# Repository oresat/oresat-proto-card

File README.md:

# "oresat-proto-card"

This is the "prototype" card for OreSat, meant to pioneer future cards and test the backplane, and be an 
easy way to hack in functionality. NOT MEANT FOR FLIGHT.

## Features

- Populates the two 1.27 mm connectors from the backplane.
- Populates all three SMPM RF connectors from the backplane.
- Standard TPS63070-bsaed buck/boost SPS (Vin = 2.5 to 7 V, Vout = 3.3V)
- Has our standard/favorite STM32F042K6 microcontroller.
   - With SWD, UART (FTDI), and CAN (to the backplane).
- Has lots of breakouts, but DO NOT POPULATE THE 0.1 IN CONNECTORS, THEY'RE TOO TALL!!!

## Connector information

- Main 1.27 mm connector ("Center" connector)
   - Samtec TFM-120-01-L-D-RA
   - https://www.digikey.com/products/en?lang=en&site=US&keywords=TFM-120-01-L-D-RA
   - Drawing: http://suddendocs.samtec.com/prints/tfm-1xx-xx-xxx-d-xxx-mkt.pdf
   - Brochure: http://suddendocs.samtec.com/catalog_english/tfm.pdf
   - 3D CAD: https://www.samtec.com/partnumber/tfm-120-01-l-d-ra?vendor=digikey#technical
   - Notes: the -RE1 model is better because of the solder stakes, but the female connector doesn't fit! The stakes get in the way :(

- Auxiliary 1.27 mm ("alt-left" connector)
   - Samtec TFM-110-01-L-D-RA

- RF (70 cm, L band, S band) conenctors
   - Card
      - Molex 73300-0030 (possible replacement is 73300-0020 but it has full detent that we don't want)
      - SMPM Connector Plug, Male Pin 50 Ohm Board Edge, Cutout; Surface Mount Solder, smooth bore
      - Molex w/3D: https://www.molex.com/molex/products/datasheet.jsp?part=active/0733000030_RF_COAX_CONNECTORS.xml
   - Barrell (connects card to backplane)
      - Molex 73300-0220 (alt but slightly different lengths: -0223, -0228)
      - SMPM female to female barrel adapter 
      - RF Adapters - In Series SMPM JACK/JACK BULLET .21IN
      - Molex w/3D: https://www.molex.com/molex/products/datasheet.jsp?part=active/0733000220_RF_COAX_CONNECTORS.xml

## LICENSE

Copyright Portland State Aerospace Society 2018.

This documentation describes Open Hardware and is licensed under the CERN OHL v. 1.2.

You may redistribute and modify this documentation under the terms of the CERN OHL v.1.2. [http://ohwr.org/cernohl](http://ohwr.org/cernohl). This documentation is distributed WITHOUT ANY EXPRESS OR IMPLIED WARRANTY, INCLUDING OF MERCHANTABILITY, SATISFACTORY QUALITY AND FITNESS FOR A PARTICULAR PURPOSE. Please see the CERN OHL v.1.2 for applicable conditions.

## Version Information

Version | Date       | Notes
--------|------------|-------------------------
3.0     | 2018/11/22 | Big changes in structure, mostly springs. Changed RF connectors to SMPM. Optimized layout for more proto area. 
2.0     | 2018/03/?? | New 1.27 mm connectors, again.
1.0     | ??         | New connectors.

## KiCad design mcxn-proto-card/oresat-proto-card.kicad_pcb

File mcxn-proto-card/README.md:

---
title: "**OreSat MCXN Proto Card**"
subtitle: |
  **Fabrication and Assembly Information**\
  For build TIME-STAMP
fontsize: 10pt
geometry:
  - margin=0.5in
toc: true
toc-depth: 2
colorlinks: true
urlcolor: blue
---

\newpage

# About this Board

## Board Description

The OreSat MCXN Proto Card is a generic OreSat card based on the NXP MCXN947 microcontroller. It has an OreSat Power Domain (OPD), 
a CAN interface, an OreSat Card Debug port, a bzillion test points, and a 0.1 inch hole prototyping area.

The proto card also has the OreSat auxiliary connector and 3 RF backplane connectors, but these are not placed since they're not usually used.

## Documentation Links

- Git repository: <https://github.com/oresat/oresat-flatsat>
- Design Notes can be found [here](https://docs.google.com/document/d/1n5go-qSHrDDtgpcY3E4sctoJmh-bkNlo19UB8_QK84I/edit?usp=sharing)

## Documentation Files

| Filename                        | Notes                                    |
| ------------------------------- | ---------------------------------------- |
| README.pdf                      | This README file                         |
| PROJECT-NAME-outline.dxf        | Board outline (with holes) in DXF format |
| PROJECT-NAME-pcba.step          | 3D model of PCBA (with components)       |
| PROJECT-NAME-render-bot.jpg     | Render of the top of the 3D model        |
| PROJECT-NAME-render-bot.jpg     | Render of the bottom of the 3D model     |
| PROJECT-NAME-schematic.pdf      | PDF of board schematics                  |

## Contact Information

- Website: <https://www.oresat.org/>
- Email: <oresat@pdx.edu>
- Instagram: @pdxaerospace

## Board Renders

{width=50%}
{width=50%}

\newpage

# Printed Circuit Board (PCB) Fabrication Information

## Board Info

- 4 layer board
- Bounding box is 99.8 x 94.6 mm
- Board thickness is 1.59 mm

## Board Requirements

- Design Rules
    - Minimum Trace / Space design rules
       - Outer layers: 0.127 mm (5.0 mil) / 0.127 mm (5.0 mil)
       - Inner layers: 0.127 mm (5.0 mil) / 0.127 mm (5.0 mil)
    - Outer dimension router tolerance: +/- 0.254 mm (10.0 mil)
    - Hole placement tolerance: +/- 0.075 mm (3.0 mil)
    - Inner tab routed slot tolerance: +/- 0.254 mm (10.0 mil)
- Drills
   - Drill Positional Tolerance: 0.051 mm (2.0 mil)
   - Drill Size tolerance: +/- 0.064 mm (2.5 mil)
- Plated/Un-plated holes
  - Via/PTH minimum diameter: 0.254 mm (10 mil)
  - Via/PTH minimum annulus: 0.102 mm (4 mil) radius
- Outline/Routing
  - This board requires a 1 mm router bit.
- Slots
  - There are no slots.
- Cutouts
  - There are no cutouts
- There are 3 fiducials on the top layer.
- Panel tabs ("mouse bites")
   - Card edges must be smooth; no mouse bites or other intrusions into the card outline.
   - If external mouse bites are required, minimize and customer will remove by hand before assembly.
- If not otherwise specified, build to IPC 6012 Class 2 or better.

## Stackup /  Materials

- Outside copper layers is 1 oz Cu after plating (0.043 mm / 1.7 mil)
- Inside copper layers are 0.5 oz Cu (0.018 mm / 0.7 mil)
- There are no requirements on the prepreg or core of this four layer stackup.
- Board Surface treatment should be ENIG, althogh immersion Silver is acceptable.
- White silkscreen on top and bottom surface
- Taiyo PSR-4000 or equivalent soldermask on top and bottom, no requirements for color.

## Array / Panel Information

- Coordinate with Contract Manufacturer (CM) for optimal size of this panel.
- If no feedback from CM, then produce single boards (no panel).

## Fabrication Files

### IPC-2581 File

| Filename                 | Notes                                   |
| ------------------------ | --------------------------------------- |
| PROJECT-NAME-ipc2581.xml | IPC-2581 board information file         |

### Legacy PCB Files

| Filename                      | Notes                                         |
| ------------------------------| --------------------------------------------- |
| PROJECT-NAME-Edge_Cuts.gbr    | RS274X file for the dimension (outline) layer |
| PROJECT-NAME-F_Silkscreen.gbr | RS274X file for the top silkscreen            |
| PROJECT-NAME-F_Mask.gbr       | RS274X file for the top soldermask            |
| PROJECT-NAME-F_Cu.gbr         | RS274X file for the top copper layer          |
| PROJECT-NAME-In1_Cu.gbr       | RS274X file for the layer 2 copper            |
| PROJECT-NAME-In2_Cu.gbr       | RS274X file for the layer 3 copper            |
| PROJECT-NAME-B_Cu.gbr         | RS274X file for the bottom copper layer       |
| PROJECT-NAME-B_Mask.gbr       | RS274X file for the bottom soldermask         |
| PROJECT-NAME-B_Silkscreen.gbr | RS274X file for the bottom silkscreen         |
| PROJECT-NAME-NPTH.drl         | Excellon file for non-plated through holes    |
| PROJECT-NAME-PTH.drl          | Excellon file for plated through holes        | 

\newpage

# Printed Circuit Board Assembly (PCBA) Information

## Assembly Info

- All components are on the top side of the board.
- This PCBA uses both surface mount (SMT) and through-hole (THT) components.

## Assembly Requirements

- Assemble to IPC Class 2 or better
- Bake components that are not moisture sealed to appropriate levels as required.
- Any solder paste (leaded or RoHS) is acceptable. RoHS solder is slightly preferred.
- Any no-clean or aqueous wash flux is acceptable.
- No conformal coating.

## Component Specific Assembly Information

- No specific information

## Assembly Files

### IPC-2581 File

| Filename                 | Notes                           |
| ------------------------ | ------------------------------- |
| PROJECT-NAME-ipc2581.xml | IPC-2581 board information file |

### Bill of Materials (BOM)

| Filename             | Description                            |
| -------------------- | -------------------------------------- |
| PROJECT-NAME-bom.csv | BOM in Comma Separated Variable format |

### Solder Paste Stencils

| Filename                 | Notes                                            |
| ------------------------ | ------------------------------------------------ |
| PROJECT-NAME-B_Paste.gbr | RS274X file for top/front solder paste stencil   |
| PROJECT-NAME-F_Paste.gbr | RS274X file for bottom/back solder paste stencil |

### Mounting/Placement Location

| Filename            | Description                                 |
| ------------------- | ------------------------------------------- |
| PROJECT-NAME.pos | Pick and place locations for components     |

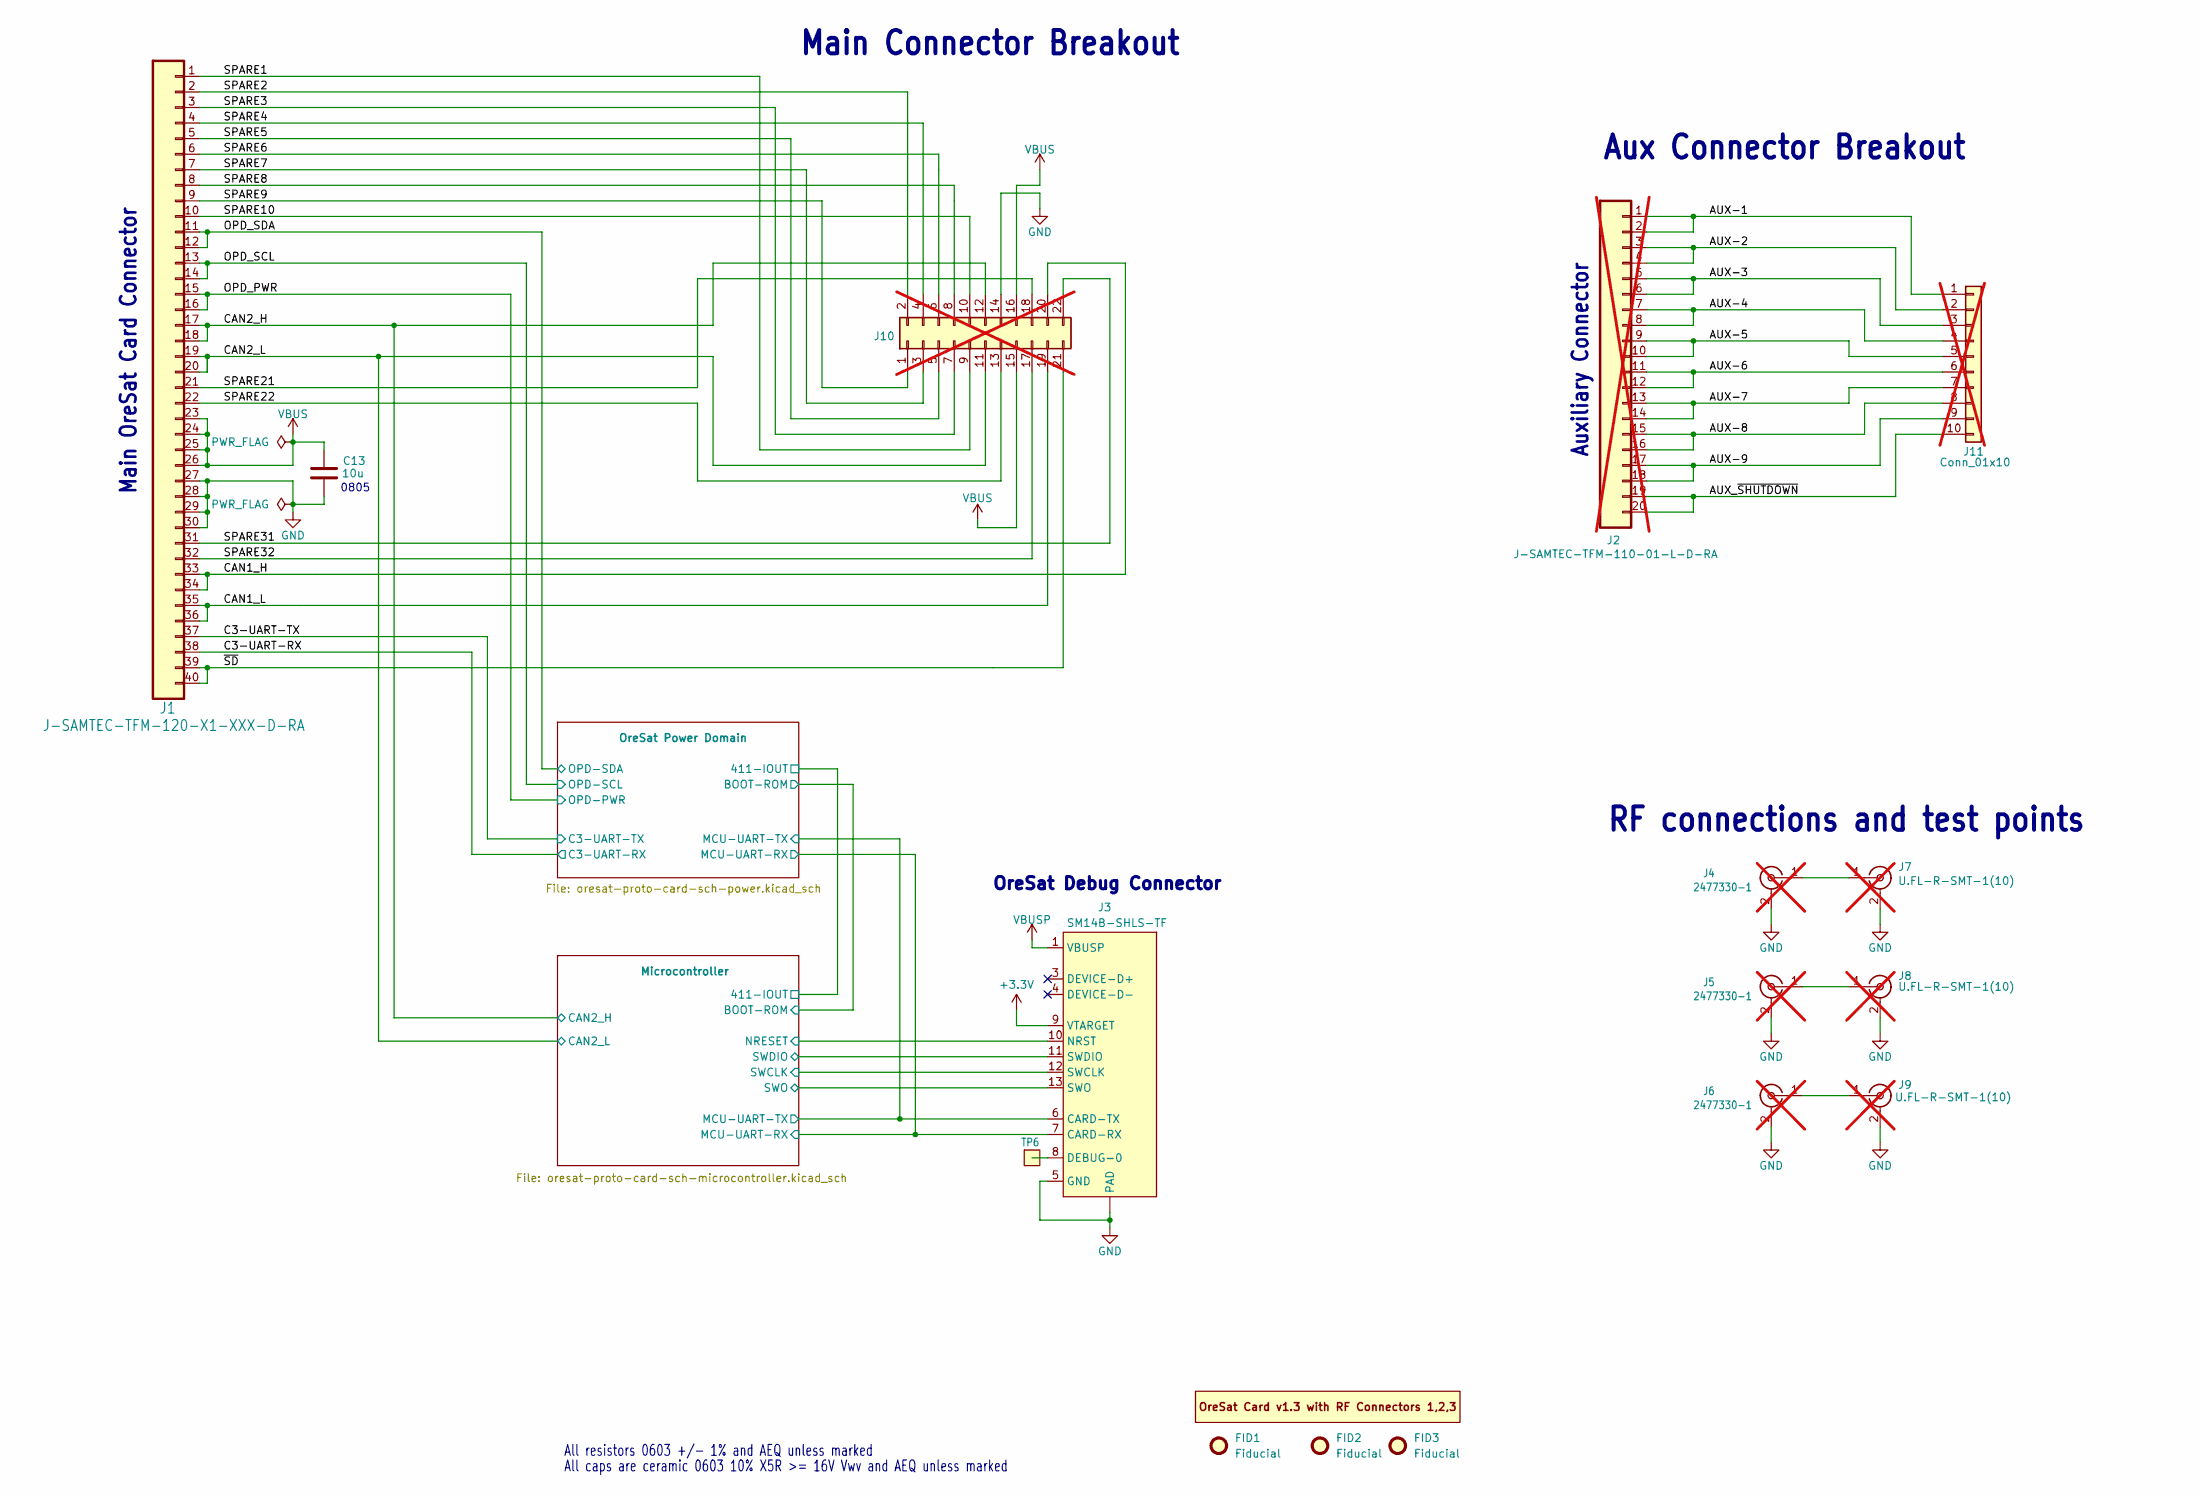
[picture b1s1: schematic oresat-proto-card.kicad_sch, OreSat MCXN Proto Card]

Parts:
C13: 10u; 0805-B-NOSILK; MPN GRT21BC71E106KE13K
FID1, FID2, FID3: Fiducial; Fiducial_1mm_Mask2mm
J1: J-SAMTEC-TFM-120-X1-XXX-D-RA; MPN TFM-120-01-L-D-RA
J2: J-SAMTEC-TFM-110-01-L-D-RA; J-SAMTEC-TFM-110-X1-XXX-D-RA; MPN TFM-110-01-L-D-RA; not fitted
J3: SM14B-SHLS-TF; J-JST-SM14BSHLSTF; MPN SM14B-SHLS-TF
J4, J5, J6: 2477330-1; J-MOLEX-SMPM-073300-002X; MPN 2477330-1; not fitted
J7, J8, J9: U.FL-R-SMT-1(10); U.FL_Hirose_U.FL-R-SMT-1_Vertical; MPN U.FL-R-SMT-1(10); not fitted
J10: PINHD-2X5; PinHeader_2x11_P2.54mm_Vertical; not fitted
J11: Conn_01x10; PinHeader_1x10_P2.54mm_Vertical; MPN 61302011121; not fitted
PCB1: ORESAT-CARD-V1.3-3RF; MPN oresat-proto-card-v6.0-2025-12-28
TP6: Test-Point; TestPoint-0.75mm-th

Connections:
+3.3V: J3.9 (VTARGET); also elsewhere on the board
/AUX-1: J2.1, J2.2, J11.1
/AUX-2: J2.3, J2.4, J11.2
/AUX-3: J2.5, J2.6, J11.3
/AUX-4: J2.7, J2.8, J11.4
/AUX-5: J2.9, J2.10, J11.5
/AUX-6: J2.11, J2.12, J11.6
/AUX-7: J2.13, J2.14, J11.7
/AUX-8: J2.15, J2.16, J11.8
/AUX-9: J2.17, J2.18, J11.9
/AUX_~SHUTDOWN: J2.19, J2.20, J11.10
/C3-UART-RX: J1.38; also elsewhere on the board
/C3-UART-TX: J1.37; also elsewhere on the board
/CAN1_H: J1.33, J1.34, J10.20
/CAN1_L: J1.35, J1.36, J10.19
/CAN2_H: J1.17, J1.18, J10.12; also elsewhere on the board
/CAN2_L: J1.19, J1.20, J10.11; also elsewhere on the board
/Microcontroller/MCU-UART-RX: J3.7 (CARD-RX); also elsewhere on the board
/Microcontroller/MCU-UART-TX: J3.6 (CARD-TX); also elsewhere on the board
/Microcontroller/NRESET: J3.10 (NRST); also elsewhere on the board
/Microcontroller/SWCLK: J3.12 (SWCLK); also elsewhere on the board
/Microcontroller/SWDIO: J3.11 (SWDIO); also elsewhere on the board
/Microcontroller/SWO: J3.13 (SWO); also elsewhere on the board
/OPD_PWR: J1.15, J1.16; also elsewhere on the board
/OPD_SCL: J1.13, J1.14; also elsewhere on the board
/OPD_SDA: J1.11, J1.12; also elsewhere on the board
/SPARE1: J1.1, J10.9
/SPARE2: J1.2, J10.2
/SPARE3: J1.3, J10.7
/SPARE4: J1.4, J10.4
/SPARE5: J1.5, J10.5
/SPARE6: J1.6, J10.6
/SPARE7: J1.7, J10.3
/SPARE8: J1.8, J10.8
/SPARE9: J1.9, J10.1
/SPARE10: J1.10, J10.10
/SPARE21: J1.21, J10.18
/SPARE22: J1.22, J10.13
/SPARE31: J1.31, J10.22
/SPARE32: J1.32, J10.17
/~SD: J1.39, J1.40, J10.21
GND: C13.2, J1.27, J1.28, J1.29, J1.30, J3.5 (GND), J3.14 (GND), J3.15 (PAD), J3.16 (PAD), J4.2 (Ext), J5.2 (Ext), J6.2 (Ext), J7.2 (Ext), J8.2 (Ext), J9.2 (Ext), J10.14; also elsewhere on the board
unnamed: J3.8 (DEBUG-0), TP6.1 (1_1)
unnamed: J4.1 (In), J7.1 (In)
unnamed: J5.1 (In), J8.1 (In)
unnamed: J6.1 (In), J9.1 (In)
VBUS: C13.1, J1.23, J1.24, J1.25, J1.26, J10.15, J10.16; also elsewhere on the board
VBUSP: J3.1 (VBUSP), J3.2 (VBUSP); also elsewhere on the board

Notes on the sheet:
All caps are ceramic 0603 10% X5R >= 16V Vwv and AEQ unless marked
All resistors 0603 +/- 1% and AEQ unless marked
0805
RF connections and test points
Main Connector Breakout
OreSat Debug Connector
Main OreSat Card Connector
Aux Connector Breakout
Auxiliary Connector

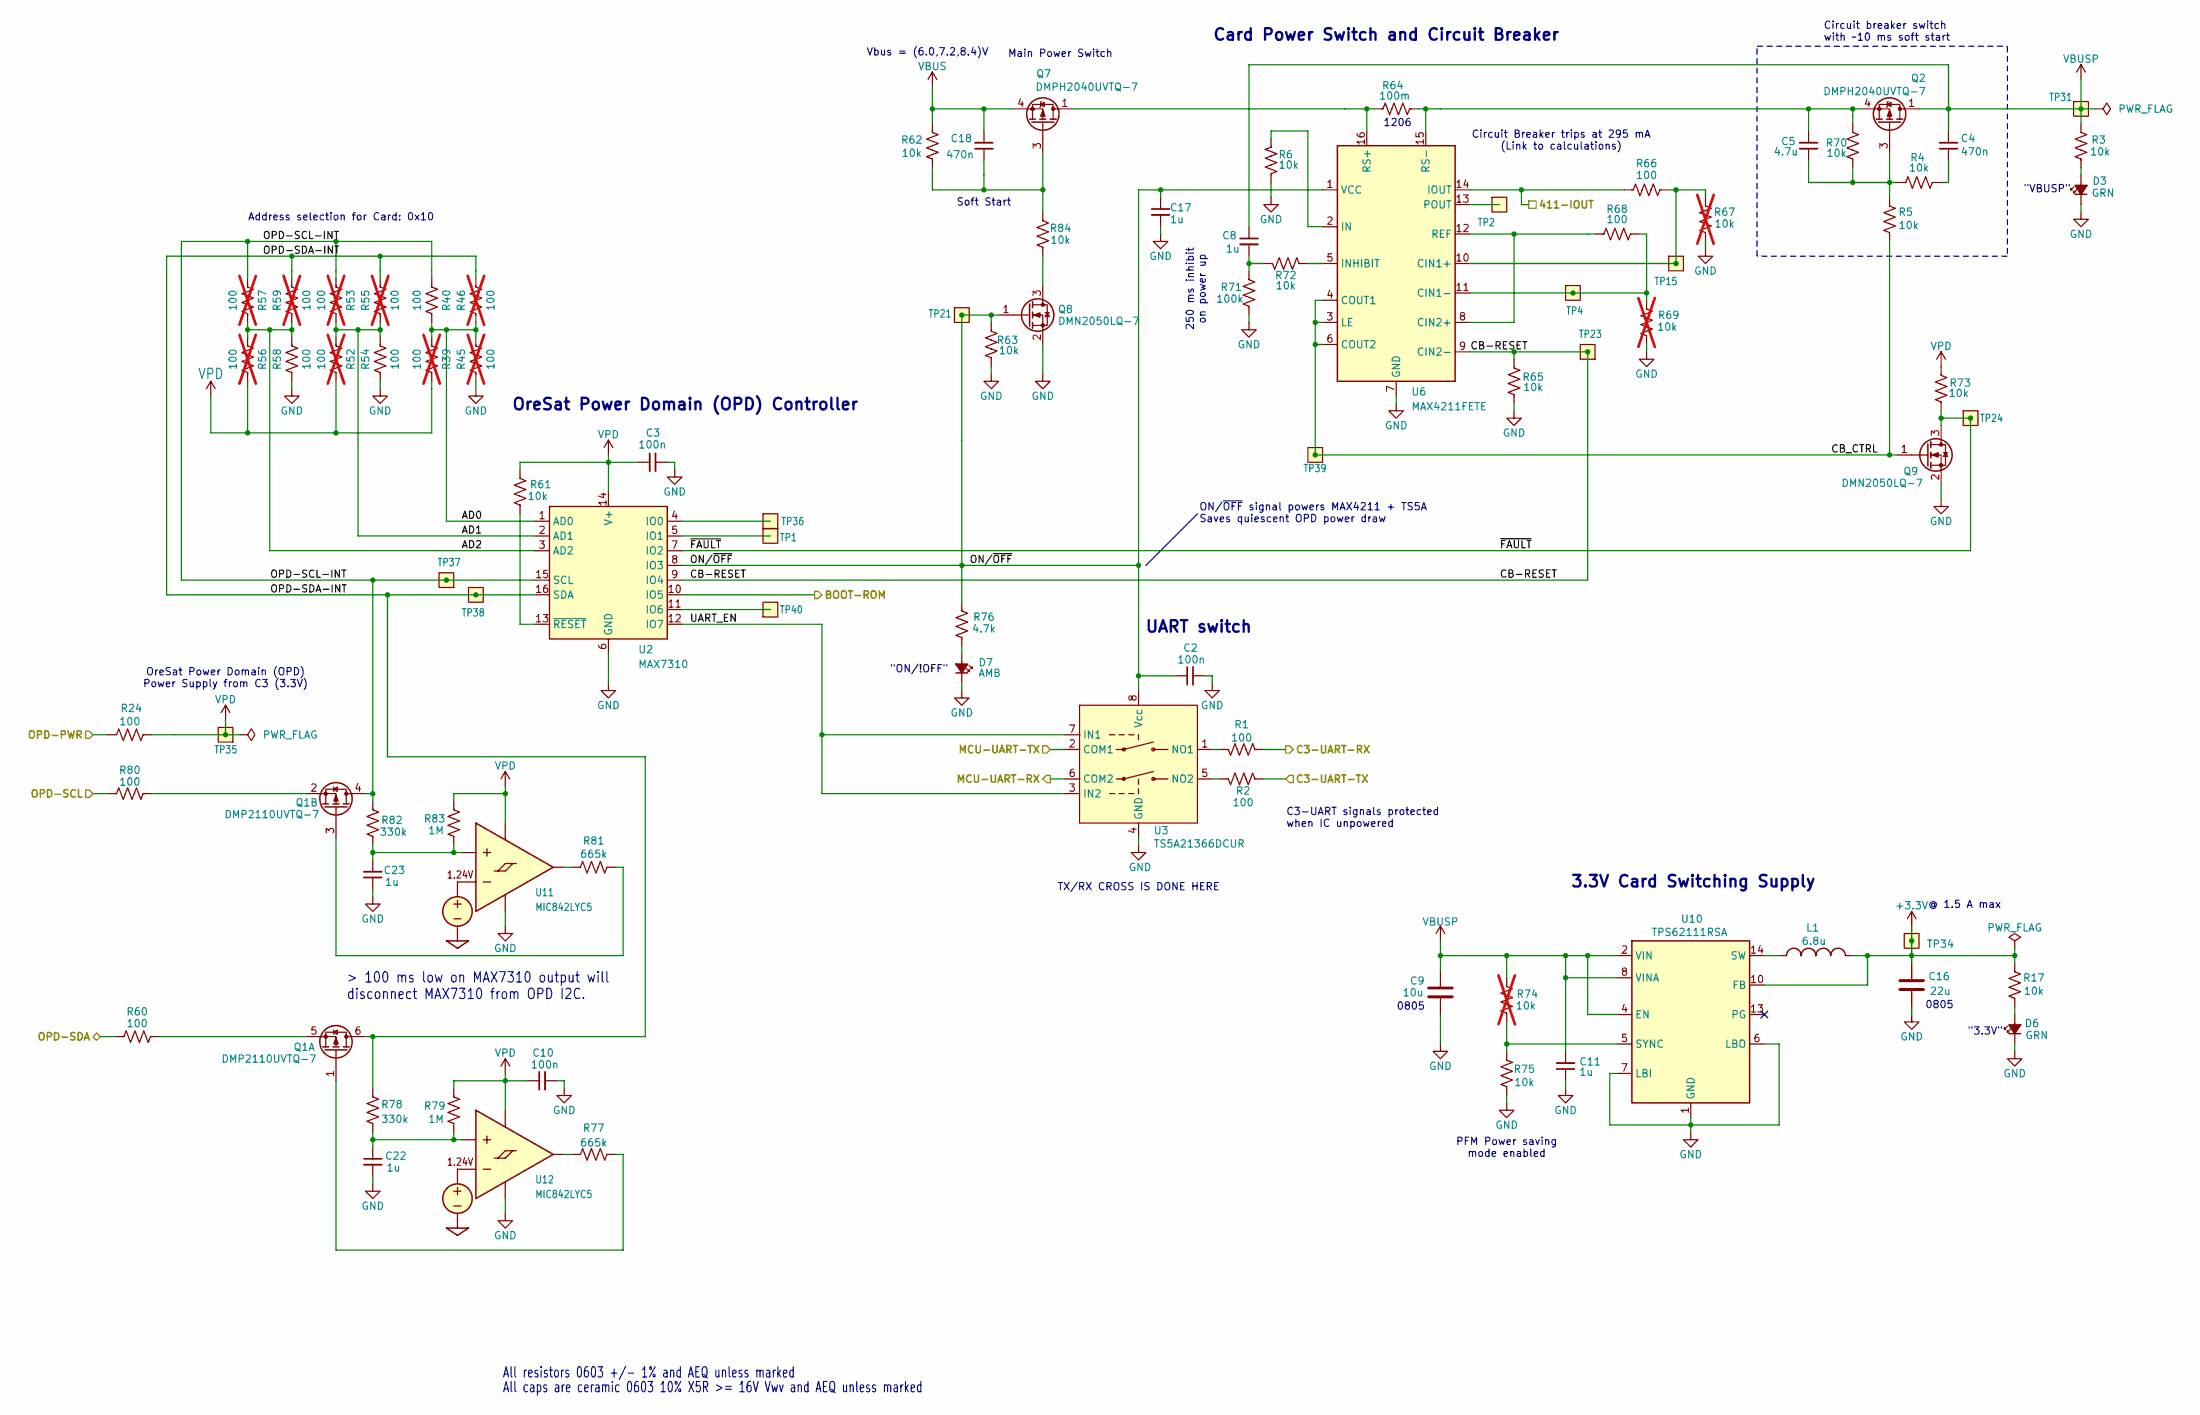
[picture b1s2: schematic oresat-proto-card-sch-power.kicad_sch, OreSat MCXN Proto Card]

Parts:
C2, C3, C10: 100n; 0603-C-NOSILK; MPN C0603C104K5RACAUTO
C4, C18: 470n; 0603-C-NOSILK; MPN C0603C474K3RACAUTO
C5: 4.7u; 0603-C-NOSILK; MPN EMK107BBJ475KAHT
C8, C11, C17, C22, C23: 1u; 0603-C-NOSILK; MPN GRT188R71E105KE13D
C9: 10u; 0805-B-NOSILK; MPN GRT21BC71E106KE13K
C16: 22u; 0805-C-NOSILK; MPN GRT21BC81C226ME13L
D3, D6: GRN; LED_0603_1608Metric; MPN 150060GS75000
D7: AMB; LED_0603_1608Metric; MPN 150060AS75000
L1: 6.8u; L_ECS-MPI4040; MPN ECS-MPI4040R4-6R8-R
Q1: DMP2110UVTQ-7; SOT-23-6; MPN DMP2110UVTQ-7
Q2, Q7: DMPH2040UVTQ-7; TSOT-23-6; MPN DMPH2040UVTQ-7
Q8, Q9: DMN2050LQ-7; SOT-23; MPN DMN2050LQ-7
R1, R2, R24, R40, R54, R58, R60, R66, R68, R80: 100; 0603-C-NOSILK; MPN RMCF0603FT100R
R3, R4, R5, R6, R17, R61, R62, R63, R65, R70, R72, R73, R75, R84: 10k; 0603-C-NOSILK; MPN RMCF0603FT10K0
R39, R45, R46, R52, R53, R55, R56, R57, R59: 100; 0603-C-NOSILK; MPN RMCF0603FT100R; not fitted
R64: 100m; R_1206_3216Metric; MPN CSR1206FKR100
R67, R69, R74: 10k; 0603-C-NOSILK; MPN RMCF0603FT10K0; not fitted
R71: 100k; 0603-C-NOSILK; MPN RMCF0603FT100K
R76: 4.7k; 0603-C-NOSILK; MPN RMCF0603FT4K70
R77, R81: 665k; 0603-C-NOSILK; MPN RMCF0603FT665K
R78, R82: 330k; 0603-C-NOSILK; MPN RMCF0603FT330K
R79, R83: 1M; 0603-C-NOSILK; MPN RMCF0603FT1M00
TP1, TP2, TP4, TP15, TP21, TP23, TP24, TP31, TP34, TP35, TP36, TP37, TP38, TP39, TP40: Test-Point; TestPoint-0.75mm-th
U2: MAX7310; QFN-16-1EP_4x4mm_P0.65mm_EP2.1x2.1mm; MPN MAX7310ATE
U3: TS5A21366DCUR; VSSOP-8_2.3x2mm_P0.5mm; MPN TS5A21366DCUR
U6: MAX4211FETE; QFN-16-1EP_4x4mm_P0.65mm_EP2.1x2.1mm; MPN MAX4211FETE
U10: TPS62111RSA; Texas_RSA_VQFN-16-1EP_4x4mm_P0.65mm_EP2.7x2.7mm; MPN TPS62111RSA
U11, U12: MIC842LYC5; SOT-353_SC-70-5; MPN MIC842LYC5-TR

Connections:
+3.3V: C16.1, L1.2, R17.2, TP34.1 (1_1), U10.10 (FB); also elsewhere on the board
/C3-UART-RX: R1.1; also elsewhere on the board
/C3-UART-TX: R2.1; also elsewhere on the board
/Microcontroller/411-IOUT: R66.2, U6.14 (IOUT); also elsewhere on the board
/Microcontroller/BOOT-ROM: U2.10 (IO5); also elsewhere on the board
/Microcontroller/MCU-UART-RX: U3.6 (COM2); also elsewhere on the board
/Microcontroller/MCU-UART-TX: U3.2 (COM1); also elsewhere on the board
/OPD_PWR: R24.1; also elsewhere on the board
/OPD_SCL: R80.1; also elsewhere on the board
/OPD_SDA: R60.1; also elsewhere on the board
/OreSat Power Domain/AD0: R39.1, R40.2, R45.2, R46.1, U2.1 (AD0)
/OreSat Power Domain/AD1: R52.1, R53.2, R54.2, R55.1, U2.2 (AD1)
/OreSat Power Domain/AD2: R56.1, R57.2, R58.2, R59.1, U2.3 (AD2)
/OreSat Power Domain/CB-RESET: R65.2, TP23.1 (1_1), U2.9 (IO4), U6.9 (CIN2-)
/OreSat Power Domain/CB_CTRL: Q9.1 (G), R5.1, TP39.1 (1_1), U6.3 (LE), U6.4 (COUT1), U6.6 (COUT2)
/OreSat Power Domain/ON/~OFF: C2.2, C17.1, Q8.1 (G), R63.2, R76.1, TP21.1 (1_1), U2.8 (IO3), U3.8 (Vcc), U6.1 (VCC)
/OreSat Power Domain/OPD-SCL-INT: Q1.4 (D), R40.1, R53.1, R57.1, R82.2, TP37.1 (1_1), U2.15 (SCL)
/OreSat Power Domain/OPD-SDA-INT: Q1.6 (D), R46.2, R55.2, R59.2, R78.2, TP38.1 (1_1), U2.16 (SDA)
/OreSat Power Domain/UART_EN: U2.12 (IO7), U3.3 (IN2), U3.7 (IN1)
/OreSat Power Domain/~FAULT: Q9.3 (D), R73.1, TP24.1 (1_1), U2.7 (IO2)
GND: C2.1, C3.1, C9.2, C10.1, C11.2, C16.2, C17.2, C22.2, C23.2, D3.1 (K), D6.1 (K), D7.1 (K), Q8.2 (S), Q9.2 (S), R6.2, R45.1, R54.1, R58.1, R63.1, R65.1, R67.1, R69.1, R71.1, R75.1, U2.6 (GND), U2.17 (GND), U3.4 (GND), U6.7 (GND), U6.17 (GND), U10.1 (GND), U10.6 (LBO), U10.7 (LBI), U10.9 (GND), U10.11 (GND), U10.12 (GND), U10.16 (GND), U10.17 (GND), U11.2 (GND), U12.2 (GND); also elsewhere on the board
unnamed: C4.1, R4.1
unnamed: C8.1, R71.2, R72.2
unnamed: D3.2 (A), R3.1
unnamed: D6.2 (A), R17.1
unnamed: D7.2 (A), R76.2
unnamed: L1.1, U10.14 (SW), U10.15 (SW)
unnamed: Q1.1 (G), R77.2
unnamed: Q1.5 (S), R60.2
unnamed: Q1.3 (G), R81.2
unnamed: Q1.2 (S), R80.2
unnamed: C5.1, Q2.3 (G), R4.2, R5.2, R70.1
unnamed: C5.2, Q2.4 (S), R64.2, R70.2, U6.15 (RS-)
unnamed: C18.2, Q7.3 (G), R62.1, R84.2
unnamed: Q8.3 (D), R84.1
unnamed: TP36.1 (1_1), U2.4 (IO0)
unnamed: TP1.1 (1_1), U2.5 (IO1)
unnamed: TP40.1 (1_1), U2.11 (IO6)
unnamed: R61.1, U2.13 (~RESET)
unnamed: R1.2, U3.1 (NO1)
unnamed: R2.2, U3.5 (NO2)
unnamed: R66.1, R67.2, TP15.1 (1_1), U6.10 (CIN1+)
unnamed: R68.1, R69.2, TP4.1 (1_1), U6.11 (CIN1-)
unnamed: R68.2, U6.8 (CIN2+), U6.12 (REF)
unnamed: R6.1, U6.2 (IN)
unnamed: R72.1, U6.5 (INHIBIT)
unnamed: TP2.1 (1_1), U6.13 (POUT)
unnamed: Q7.1 (D), Q7.2 (D), Q7.5 (D), Q7.6 (D), R64.1, U6.16 (RS+)
unnamed: R74.1, R75.2, U10.5 (SYNC)
unnamed: C23.1, R82.1, R83.1, U11.1 (INP)
unnamed: R81.1, U11.4 (OUT)
unnamed: C22.1, R78.1, R79.1, U12.1 (INP)
unnamed: R77.1, U12.4 (OUT)
VBUS: C18.1, Q7.4 (S), R62.2; also elsewhere on the board
VBUSP: C4.2, C8.2, C9.1, C11.1, Q2.1 (D), Q2.2 (D), Q2.5 (D), Q2.6 (D), R3.2, R74.2, TP31.1 (1_1), U10.2 (VIN), U10.3 (VIN), U10.4 (EN), U10.8 (VINA); also elsewhere on the board
VPD: C3.2, C10.2, R24.2, R39.2, R52.2, R56.2, R61.2, R73.2, R79.2, R83.2, TP35.1 (1_1), U2.14 (V+), U11.5 (VDD), U12.5 (VDD)

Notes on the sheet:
ON/~{OFF} signal powers MAX4211 + TS5A Saves quiescent OPD power draw
Circuit Breaker trips at 295 mA (Link to calculations)
Card Power Switch and Circuit Breaker
1206
3.3V Card Switching Supply
"3.3V"
> 100 ms low on MAX7310 output will disconnect MAX7310 from OPD I2C.
C3-UART signals protected when IC unpowered
OreSat Power Domain (OPD) Power Supply from C3 (3.3V)
Vbus = (6.0,7.2,8.4)V
All resistors 0603 +/- 1% and AEQ unless marked
0805
OreSat Power Domain (OPD) Controller
"VBUSP"
All caps are ceramic 0603 10% X5R >= 16V Vwv and AEQ unless marked
250 ms inhibit on power up
@ 1.5 A max
Soft Start
PFM Power saving mode enabled
"ON/!OFF"
TX/RX CROSS IS DONE HERE
Address selection for Card: 0x10
Circuit breaker switch with ~10 ms soft start
Main Power Switch
UART switch

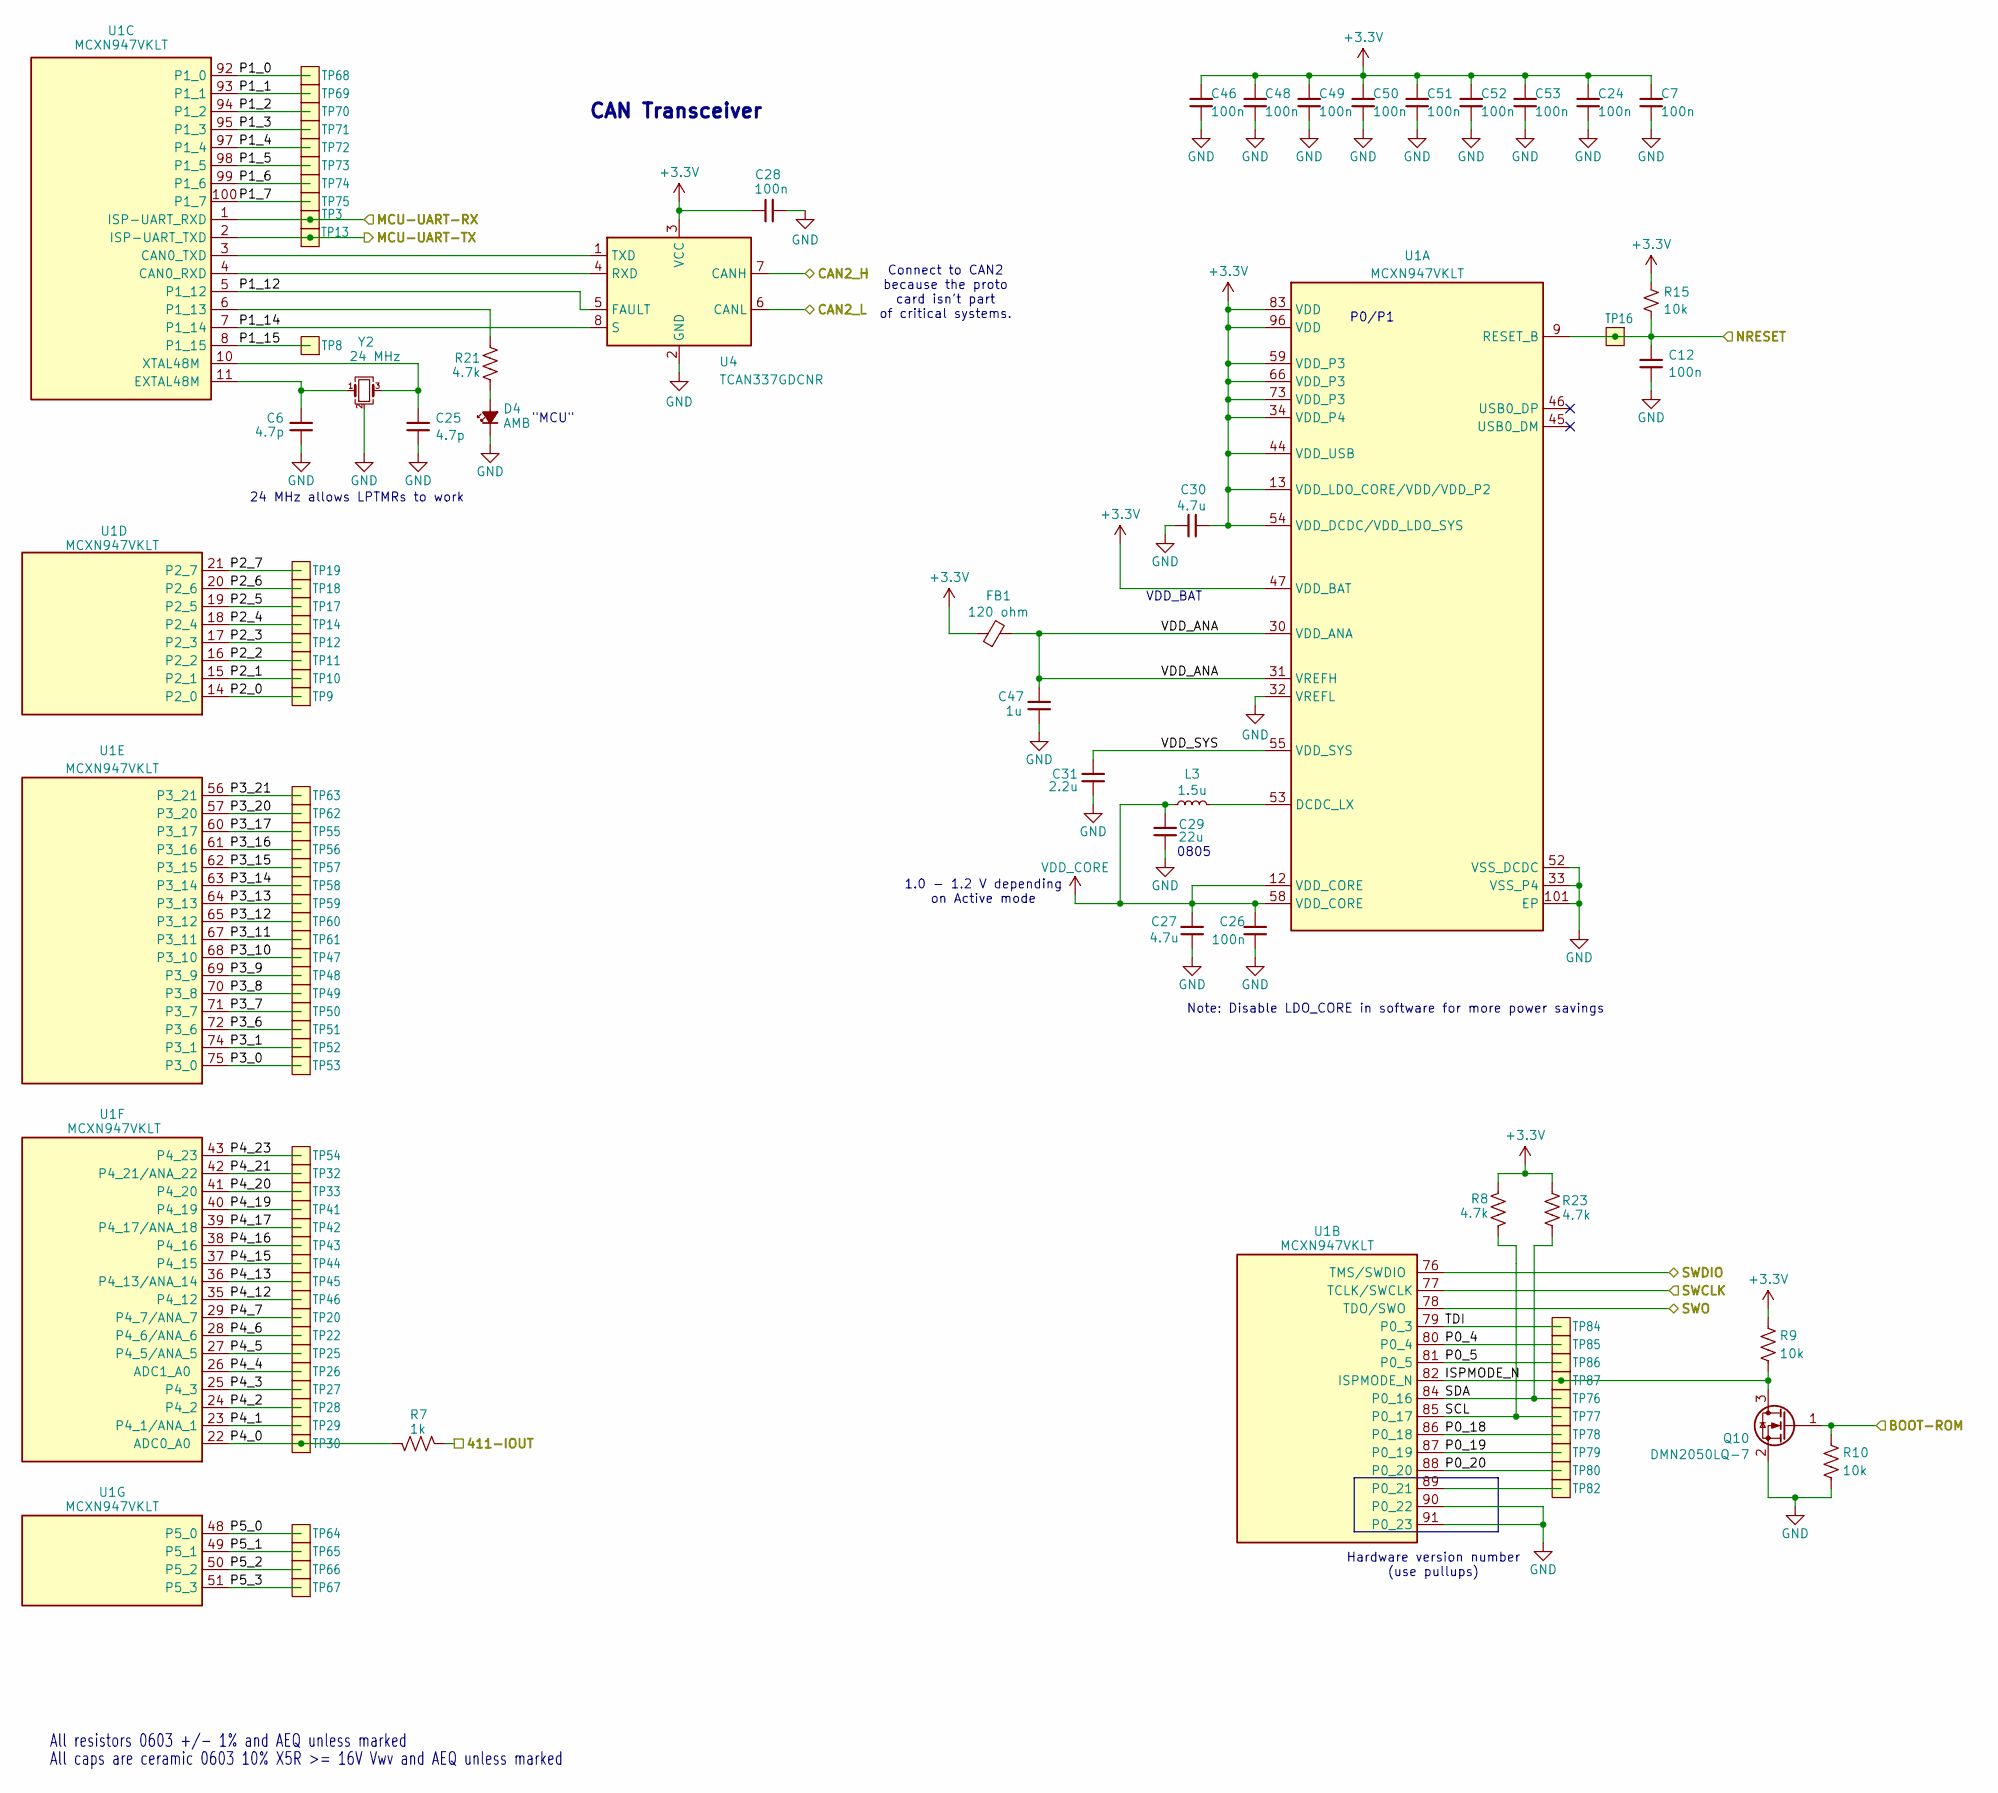
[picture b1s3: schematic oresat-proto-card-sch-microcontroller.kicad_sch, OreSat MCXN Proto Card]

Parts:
C6, C25: 4.7p; 0603-C-NOSILK; MPN C0603C479D5GACAUTO
C7, C12, C24, C26, C28, C46, C48, C49, C50, C51, C52, C53: 100n; 0603-C-NOSILK; MPN C0603C104K5RACAUTO
C27, C30: 4.7u; 0603-C-NOSILK; MPN EMK107BBJ475KAHT
C29: 22u; 0805-C-NOSILK; MPN GRT21BC81C226ME13L
C31: 2.2u; 0603-C-NOSILK; MPN GRT188C71E225KE13D
C47: 1u; 0603-C-NOSILK; MPN GRT188R71E105KE13D
D4: AMB; LED_0603_1608Metric; MPN 150060AS75000
FB1: 120 ohm; 0805-B-NOSILK; MPN 2508051217Y6
L3: 1.5u; L_0805_2012Metric; MPN SRP2012TMA-1R5M
Q10: DMN2050LQ-7; SOT-23; MPN DMN2050LQ-7
R7: 1k; 0603-C-NOSILK; MPN RMCF0603FT1K00
R8, R21, R23: 4.7k; 0603-C-NOSILK; MPN RMCF0603FT4K70
R9, R10, R15: 10k; 0603-C-NOSILK; MPN RMCF0603FT10K0
TP3, TP8, TP9, TP10, TP11, TP12, TP13, TP14, TP16, TP17, TP18, TP19, TP20, TP22, TP25, TP26, TP27, TP28, TP29, TP30, TP32, TP33, TP41, TP42, TP43, TP44, TP45, TP46, TP47, TP48, TP49, TP50, TP51, TP52, TP53, TP54, TP55, TP56, TP57, TP58, TP59, TP60, TP61, TP62, TP63, TP64, TP65, TP66, TP67, TP68, TP69, TP70, TP71, TP72, TP73, TP74, TP75, TP76, TP77, TP78, TP79, TP80, TP82, TP84, TP85, TP86, TP87: Test-Point; TestPoint-0.75mm-th
U1: MCXN947VKLT; MCXN947KVLT-QFP50P1600X1600X160-101N; MPN MCXN947VKLT
U4: TCAN337GDCNR; SOT-23-8; MPN TCAN337GDCNR
Y2: 24 MHz; Crystal_SMD_2016-4Pin_2.0x1.6mm; MPN 830108212309

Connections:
+3.3V: C7.1, C24.1, C28.1, C30.1, C46.1, C48.1, C49.1, C50.1, C51.1, C52.1, C53.1, FB1.1, R8.2, R9.2, R15.2, R23.2, U1.13 (VDD_LDO_CORE/VDD/VDD_P2), U1.34 (VDD_P4), U1.44 (VDD_USB), U1.47 (VDD_BAT), U1.54 (VDD_DCDC/VDD_LDO_SYS), U1.59 (VDD_P3), U1.66 (VDD_P3), U1.73 (VDD_P3), U1.83 (VDD), U1.96 (VDD), U4.3 (VCC); also elsewhere on the board
/CAN2_H: U4.7 (CANH); also elsewhere on the board
/CAN2_L: U4.6 (CANL); also elsewhere on the board
/Microcontroller/411-IOUT: R7.2; also elsewhere on the board
/Microcontroller/BOOT-ROM: Q10.1 (G), R10.2; also elsewhere on the board
/Microcontroller/ISPMODE_N: Q10.3 (D), R9.1, TP87.1 (1_1), U1.82 (ISPMODE_N)
/Microcontroller/MCU-UART-RX: TP3.1 (1_1), U1.1 (ISP-UART_RXD); also elsewhere on the board
/Microcontroller/MCU-UART-TX: TP13.1 (1_1), U1.2 (ISP-UART_TXD); also elsewhere on the board
/Microcontroller/NRESET: C12.1, R15.1, TP16.1 (1_1), U1.9 (RESET_B); also elsewhere on the board
/Microcontroller/P0_4: TP85.1 (1_1), U1.80 (P0_4)
/Microcontroller/P0_5: TP86.1 (1_1), U1.81 (P0_5)
/Microcontroller/P0_18: TP78.1 (1_1), U1.86 (P0_18)
/Microcontroller/P0_19: TP79.1 (1_1), U1.87 (P0_19)
/Microcontroller/P0_20: TP80.1 (1_1), U1.88 (P0_20)
/Microcontroller/P1_0: TP68.1 (1_1), U1.92 (P1_0)
/Microcontroller/P1_1: TP69.1 (1_1), U1.93 (P1_1)
/Microcontroller/P1_2: TP70.1 (1_1), U1.94 (P1_2)
/Microcontroller/P1_3: TP71.1 (1_1), U1.95 (P1_3)
/Microcontroller/P1_4: TP72.1 (1_1), U1.97 (P1_4)
/Microcontroller/P1_5: TP73.1 (1_1), U1.98 (P1_5)
/Microcontroller/P1_6: TP74.1 (1_1), U1.99 (P1_6)
/Microcontroller/P1_7: TP75.1 (1_1), U1.100 (P1_7)
/Microcontroller/P1_12: U1.5 (P1_12), U4.5 (FAULT)
/Microcontroller/P1_14: U1.7 (P1_14), U4.8 (S)
/Microcontroller/P1_15: TP8.1 (1_1), U1.8 (P1_15)
/Microcontroller/P2_0: TP9.1 (1_1), U1.14 (P2_0)
/Microcontroller/P2_1: TP10.1 (1_1), U1.15 (P2_1)
/Microcontroller/P2_2: TP11.1 (1_1), U1.16 (P2_2)
/Microcontroller/P2_3: TP12.1 (1_1), U1.17 (P2_3)
/Microcontroller/P2_4: TP14.1 (1_1), U1.18 (P2_4)
/Microcontroller/P2_5: TP17.1 (1_1), U1.19 (P2_5)
/Microcontroller/P2_6: TP18.1 (1_1), U1.20 (P2_6)
/Microcontroller/P2_7: TP19.1 (1_1), U1.21 (P2_7)
/Microcontroller/P3_0: TP53.1 (1_1), U1.75 (P3_0)
/Microcontroller/P3_1: TP52.1 (1_1), U1.74 (P3_1)
/Microcontroller/P3_6: TP51.1 (1_1), U1.72 (P3_6)
/Microcontroller/P3_7: TP50.1 (1_1), U1.71 (P3_7)
/Microcontroller/P3_8: TP49.1 (1_1), U1.70 (P3_8)
/Microcontroller/P3_9: TP48.1 (1_1), U1.69 (P3_9)
/Microcontroller/P3_10: TP47.1 (1_1), U1.68 (P3_10)
/Microcontroller/P3_11: TP61.1 (1_1), U1.67 (P3_11)
/Microcontroller/P3_12: TP60.1 (1_1), U1.65 (P3_12)
/Microcontroller/P3_13: TP59.1 (1_1), U1.64 (P3_13)
/Microcontroller/P3_14: TP58.1 (1_1), U1.63 (P3_14)
/Microcontroller/P3_15: TP57.1 (1_1), U1.62 (P3_15)
/Microcontroller/P3_16: TP56.1 (1_1), U1.61 (P3_16)
/Microcontroller/P3_17: TP55.1 (1_1), U1.60 (P3_17)
/Microcontroller/P3_20: TP62.1 (1_1), U1.57 (P3_20)
/Microcontroller/P3_21: TP63.1 (1_1), U1.56 (P3_21)
/Microcontroller/P4_0: R7.1, TP30.1 (1_1), U1.22 (ADC0_A0)
/Microcontroller/P4_1: TP29.1 (1_1), U1.23 (P4_1/ANA_1)
/Microcontroller/P4_2: TP28.1 (1_1), U1.24 (P4_2)
/Microcontroller/P4_3: TP27.1 (1_1), U1.25 (P4_3)
/Microcontroller/P4_4: TP26.1 (1_1), U1.26 (ADC1_A0)
/Microcontroller/P4_5: TP25.1 (1_1), U1.27 (P4_5/ANA_5)
/Microcontroller/P4_6: TP22.1 (1_1), U1.28 (P4_6/ANA_6)
/Microcontroller/P4_7: TP20.1 (1_1), U1.29 (P4_7/ANA_7)
/Microcontroller/P4_12: TP46.1 (1_1), U1.35 (P4_12)
/Microcontroller/P4_13: TP45.1 (1_1), U1.36 (P4_13/ANA_14)
/Microcontroller/P4_15: TP44.1 (1_1), U1.37 (P4_15)
/Microcontroller/P4_16: TP43.1 (1_1), U1.38 (P4_16)
/Microcontroller/P4_17: TP42.1 (1_1), U1.39 (P4_17/ANA_18)
/Microcontroller/P4_19: TP41.1 (1_1), U1.40 (P4_19)
/Microcontroller/P4_20: TP33.1 (1_1), U1.41 (P4_20)
/Microcontroller/P4_21: TP32.1 (1_1), U1.42 (P4_21/ANA_22)
/Microcontroller/P4_23: TP54.1 (1_1), U1.43 (P4_23)
/Microcontroller/P5_0: TP64.1 (1_1), U1.48 (P5_0)
/Microcontroller/P5_1: TP65.1 (1_1), U1.49 (P5_1)
/Microcontroller/P5_2: TP66.1 (1_1), U1.50 (P5_2)
/Microcontroller/P5_3: TP67.1 (1_1), U1.51 (P5_3)
/Microcontroller/SCL: R8.1, TP77.1 (1_1), U1.85 (P0_17)
/Microcontroller/SDA: R23.1, TP76.1 (1_1), U1.84 (P0_16)
/Microcontroller/SWCLK: U1.77 (TCLK/SWCLK); also elsewhere on the board
/Microcontroller/SWDIO: U1.76 (TMS/SWDIO); also elsewhere on the board
/Microcontroller/SWO: U1.78 (TDO/SWO); also elsewhere on the board
/Microcontroller/TDI: TP84.1 (1_1), U1.79 (P0_3)
/Microcontroller/VDD_ANA: C47.1, FB1.2, U1.30 (VDD_ANA), U1.31 (VREFH)
/Microcontroller/VDD_SYS: C31.1, U1.55 (VDD_SYS)
GND: C6.2, C7.2, C12.2, C24.2, C25.2, C26.2, C27.2, C28.2, C29.2, C30.2, C31.2, C46.2, C47.2, C48.2, C49.2, C50.2, C51.2, C52.2, C53.2, D4.1 (K), Q10.2 (S), R10.1, U1.32 (VREFL), U1.33 (VSS_P4), U1.52 (VSS_DCDC), U1.90 (P0_22), U1.91 (P0_23), U1.101 (EP), U4.2 (GND), Y2.2 (G), Y2.4 (G); also elsewhere on the board
unnamed: D4.2 (A), R21.2
unnamed: L3.2, U1.53 (DCDC_LX)
unnamed: TP82.1 (1_1), U1.89 (P0_21)
unnamed: U1.3 (CAN0_TXD), U4.1 (TXD)
unnamed: U1.4 (CAN0_RXD), U4.4 (RXD)
unnamed: R21.1, U1.6 (P1_13)
unnamed: C25.1, U1.10 (XTAL48M), Y2.3
unnamed: C6.1, U1.11 (EXTAL48M), Y2.1
VDD_CORE: C26.1, C27.1, C29.1, L3.1, U1.12 (VDD_CORE), U1.58 (VDD_CORE)

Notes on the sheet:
Connect to CAN2 because the proto card isn't part of critical systems.
All caps are ceramic 0603 10% X5R >= 16V Vwv and AEQ unless marked
Hardware version number (use pullups)
Note: Disable LDO_CORE in software for more power savings
All resistors 0603 +/- 1% and AEQ unless marked
24 MHz allows LPTMRs to work
0805
1.0 - 1.2 V depending on Active mode
VDD_BAT
"MCU"
P0/P1
CAN Transceiver
